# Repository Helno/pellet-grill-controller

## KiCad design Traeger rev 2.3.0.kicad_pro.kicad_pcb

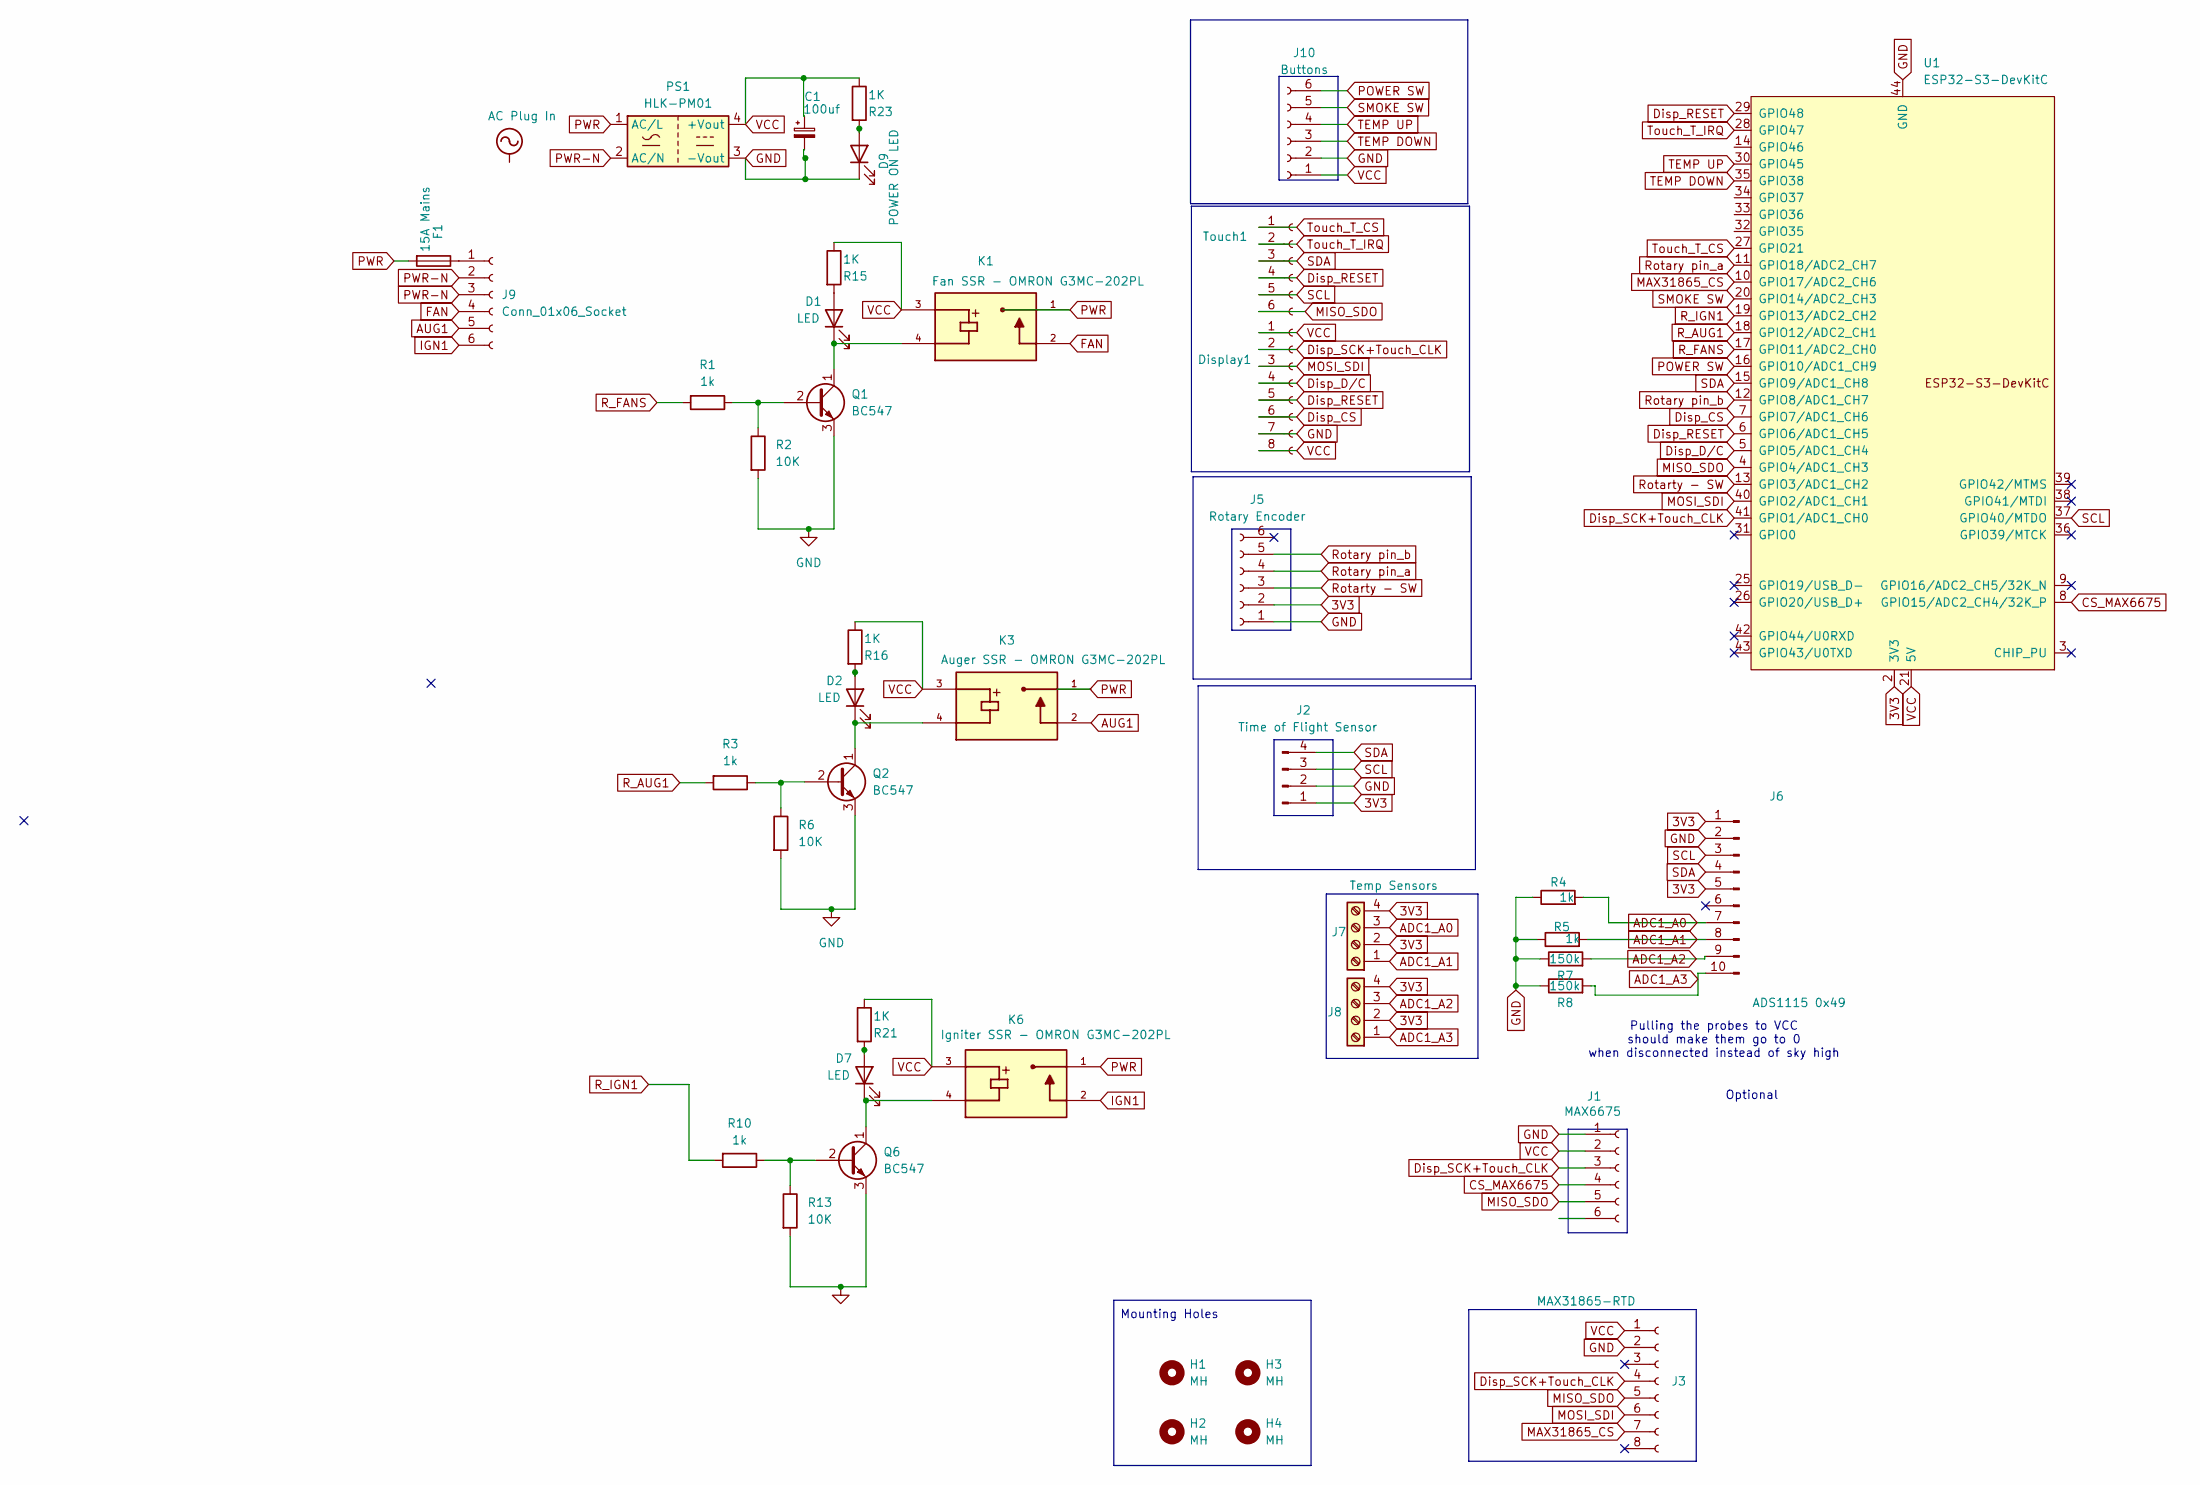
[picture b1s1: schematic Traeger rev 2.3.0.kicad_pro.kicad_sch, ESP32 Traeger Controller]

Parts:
C1: 100uf; CP_Radial_D8.0mm_P3.50mm
D1, D2, D7: LED; LED_D3.0mm
D9: POWER ON LED; LED_D3.0mm
Display1: Conn_01x08_Socket; JST_EH_B8B-EH-A_1x08_P2.50mm_Vertical
F1: 15A Mains; Fuse Block 3544-2_KEYSTONE
H1, H2, H3, H4: MH; MountingHole_3.2mm_M3
J1: MAX6675; JST_XH_B6B-XH-A_1x06_P2.50mm_Vertical
J2: Time of Flight Sensor; JST_EH_B4B-EH-A_1x04_P2.50mm_Vertical
J3: MAX31865-RTD; PinSocket_1x08_P2.54mm_Vertical
J5: Rotary Encoder; JST_XH_B6B-XH-A_1x06_P2.50mm_Vertical
J6: ADS1115 0x49; PinSocket_1x10_P2.54mm_Vertical
J7, J8: Temp Sensors; TerminalBlock_RND_205-00014_1x04_P5.00mm_Horizontal
J9: Conn_01x06_Socket; TerminalBlock_RND_205-00005_1x06_P5.00mm_Horizontal
J10: Buttons; JST_XH_B6B-XH-A_1x06_P2.50mm_Vertical
K1: Fan SSR - OMRON G3MC-202PL; RELAY_G3MB-202PDC5; PARTREV J091-E1-1A
K3: Auger SSR - OMRON G3MC-202PL; RELAY_G3MB-202PDC5; PARTREV J091-E1-1A
K6: Igniter SSR - OMRON G3MC-202PL; RELAY_G3MB-202PDC5; PARTREV J091-E1-1A
PS1: HLK-PM01; Converter_ACDC_Hi-Link_HLK-PMxx
Q1, Q2, Q6: BC547; TO-92L_Inline
R1, R3, R4, R5, R10: 1k; R_Axial_DIN0207_L6.3mm_D2.5mm_P7.62mm_Horizontal
R2, R6, R13: 10K; R_Axial_DIN0207_L6.3mm_D2.5mm_P7.62mm_Horizontal
R7, R8: 150k; R_Axial_DIN0207_L6.3mm_D2.5mm_P7.62mm_Horizontal
R15, R16, R21, R23: 1K; R_Axial_DIN0207_L6.3mm_D2.5mm_P7.62mm_Horizontal
Touch1: Conn_01x06_Socket; JST_EH_B6B-EH-A_1x06_P2.50mm_Vertical
U1: ESP32-S3-DevKitC

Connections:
3V3: J2.1, J5.2, J6.1, J6.5, J7.2, J7.4, J8.2, J8.4, U1.1 (3V3), U1.2 (3V3)
ADC1_A0: J6.7, J7.3, R4.2
ADC1_A1: J6.8, J7.1, R5.2
ADC1_A2: J6.9, J8.3, R7.2
ADC1_A3: J6.10, J8.1, R8.2
AUG1: J9.5, K3.2
CS_MAX6675: J1.4, U1.8 (GPIO15/ADC2_CH4/32K_P)
Disp_CS: Display1.6, U1.7 (GPIO7/ADC1_CH6)
Disp_D/C: Display1.4, U1.5 (GPIO5/ADC1_CH4)
Disp_RESET: Display1.5, Touch1.4, U1.6 (GPIO6/ADC1_CH5), U1.29 (GPIO48)
Disp_SCK+Touch_CLK: Display1.2, J1.3, J3.4, U1.41 (GPIO1/ADC1_CH0)
FAN: J9.4, K1.2
GND: C1.2, D9.1 (K), Display1.7, J1.1, J2.2, J3.2, J5.1, J6.2, J10.2, PS1.3 (-Vout), Q1.3 (E), Q2.3 (E), Q6.3 (E), R2.2, R4.1, R5.1, R6.2, R7.1, R8.1, R13.2, U1.22 (GND), U1.23 (GND), U1.24 (GND), U1.44 (GND)
IGN1: J9.6, K6.2
MAX31865_CS: J3.7, U1.10 (GPIO17/ADC2_CH6)
MISO_SDO: J1.5, J3.5, Touch1.6, U1.4 (GPIO4/ADC1_CH3)
MOSI_SDI: Display1.3, J3.6, U1.40 (GPIO2/ADC1_CH1)
unnamed: D1.2 (A), R15.2
unnamed: D1.1 (K), K1.4, Q1.1 (C)
unnamed: D2.2 (A), R16.2
unnamed: D2.1 (K), K3.4, Q2.1 (C)
unnamed: D7.2 (A), R21.2
unnamed: D7.1 (K), K6.4, Q6.1 (C)
unnamed: D9.2 (A), R23.2
unnamed: F1.1, J9.1
unnamed: Q1.2 (B), R1.1, R2.1
unnamed: Q2.2 (B), R3.1, R6.1
unnamed: Q6.2 (B), R10.1, R13.1
POWER SW: J10.6, U1.16 (GPIO10/ADC1_CH9)
PWR: F1.2, K1.1, K3.1, K6.1, PS1.1 (AC/L)
PWR-N: J9.2, J9.3, PS1.2 (AC/N)
R_AUG1: R3.2, U1.18 (GPIO12/ADC2_CH1)
R_FANS: R1.2, U1.17 (GPIO11/ADC2_CH0)
R_IGN1: R10.2, U1.19 (GPIO13/ADC2_CH2)
Rotarty - SW: J5.3, U1.13 (GPIO3/ADC1_CH2)
Rotary pin_a: J5.4, U1.11 (GPIO18/ADC2_CH7)
Rotary pin_b: J5.5, U1.12 (GPIO8/ADC1_CH7)
SCL: J2.3, J6.3, Touch1.5, U1.37 (GPIO40/MTDO)
SDA: J2.4, J6.4, Touch1.3, U1.15 (GPIO9/ADC1_CH8)
SMOKE SW: J10.5, U1.20 (GPIO14/ADC2_CH3)
TEMP DOWN: J10.3, U1.35 (GPIO38)
TEMP UP: J10.4, U1.30 (GPIO45)
Touch_T_CS: Touch1.1, U1.27 (GPIO21)
Touch_T_IRQ: Touch1.2, U1.28 (GPIO47)
VCC: C1.1, Display1.1, Display1.8, J1.2, J3.1, J10.1, K1.3, K3.3, K6.3, PS1.4 (+Vout), R15.1, R16.1, R21.1, R23.1, U1.21 (5V)

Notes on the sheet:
Pulling the probes to VCC should make them go to 0 when disconnected instead of sky high
Optional
Mounting Holes

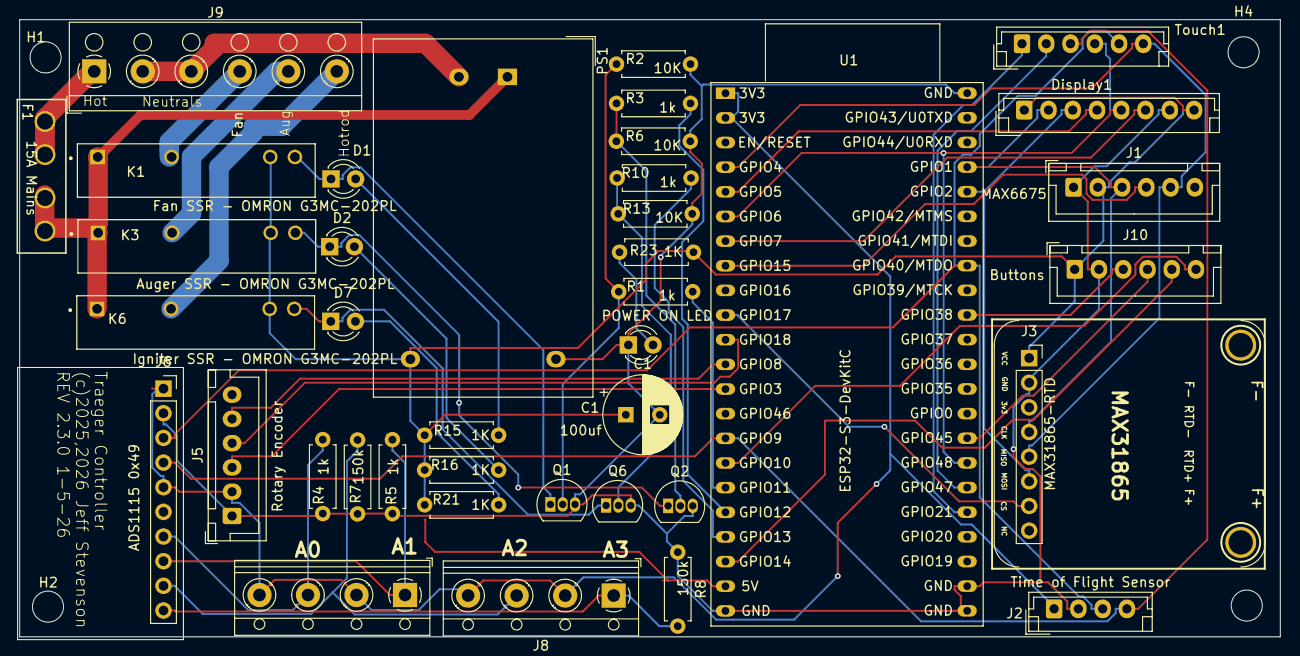
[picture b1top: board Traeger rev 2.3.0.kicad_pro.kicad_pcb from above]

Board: 2 copper layers, 129.9 x 63.6 mm, 45 parts (0 on the bottom side), 45 nets.

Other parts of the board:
U$18, U$19: MOUNTINGHOLE2.5; MOUNTINGHOLE_2.5_PLATED

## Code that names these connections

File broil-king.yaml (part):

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touchscreen:
  - platform: ft63x6
    i2c_id: i2c_bus
    interrupt_pin: GPIO47
    reset_pin: GPIO48
    id: my_touchscreen
    #update_interval: 25ms
    calibration:
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
spi:
  - id: spi_bus
    clk_pin: GPIO1 #display SCK/touch T_CLK
    mosi_pin: GPIO2 #SDI-max / display /touch T_DIN
    miso_pin: GPIO4 #SDO-max / touch T_DO, display doesnt need MISO

display:
  - platform: ili9xxx
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    spi_id: spi_bus
    data_rate: 40MHz
    model: ILI9488_A #TFT 3.5  
    dc_pin: GPIO5    
    cs_pin: GPIO7 
    reset_pin: GPIO6 #pin 5 display
    color_palette: 8BIT
    #LED - jumper to VCC so it is always on
    rotation: 90
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          }
i2c: 
  - id:  i2c_bus
    sda: GPIO9
    scl: GPIO40
    scan: true
    #frequency: 100000
    #timeout: 100ms
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  - platform: max6675
    name: "FirePot Temperature"
    id: firepot_temperature
    cs_pin: GPIO15
    update_interval: 5s

  - platform: max31865
    #name: "RTD Temperature raw"
    id: rtd_temperature_c
    cs_pin: GPIO17 
    spi_id: spi_bus 
    reference_resistance: "4280 Ω"
    rtd_nominal_resistance: "1000 Ω"
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  - platform: rotary_encoder
    name: "Rotary Encoder"
    pin_a: 
      number: GPIO18 
      inverted: true
    pin_b: 
      number: GPIO8 
      inverted: false
    id: rotary
    on_clockwise:
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            - script.execute: sc_pot_heating
#      
  - platform: gpio
    pin: GPIO11
    name: "-Fans On/Off"
    inverted: no
    id: fans_on_off_sw
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                id(fans_on_off_sw)->publish_state(false);

  - platform: gpio
    pin: GPIO12
    name: "-Auger 1 SW"
    inverted: no
    id: auger_1_sw
    restore_mode: ALWAYS_OFF

  - platform: gpio
    pin: GPIO13
    name: "-HotRod 1 SW"
    inverted: no
    id: hotrod_1_sw
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
  - platform: gpio
    pin:
      number: GPIO10
      mode:
        input: true
    name: "Power Button"
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
  - platform: gpio
    pin:
      number: GPIO14
      mode:
        input: true
    name: "Smoke Mode Button"
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
  - platform: gpio
    pin:
      number: GPIO38
      mode:
        input: true
    name: "Temperature Down"
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
  - platform: gpio
    pin:
      number: GPIO45
      mode:
        input: true
    name: "Temperature Up"
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
  - platform: gpio
    pin: 
      number: GPIO3
      mode:
        input: true
        pullup: true
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
  # - platform: gpio
  #   pin: 
  #     number: GPIO11
  #     mode:
  #       input: true
  #   name: "Power On Button"
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          
  # - platform: gpio
  #   pin: 
  #     number: GPIO12
  #     mode:
  #       input: true
  #   name: "Smoke On/Off Button" 
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
  # - platform: gpio
  #   pin: 
  #     number: GPIO13
  #     mode:
  #       input: true
  #   name: "Temperature Up Button"
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

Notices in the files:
Traeger rev 2.3.0.kicad_pro.kicad_pcb:
(c)2025,2026 Jeff Stevenson
